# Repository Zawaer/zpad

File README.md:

# ZPad

A 8-key macropad powered by a RP2040, featuring a rotary encoder and a 0.91" OLED display.

Built through [Hack Club](https://hackclub.com)'s Hackpad program. The OLED animation engine in the firmware (bouncing balls, starfield, digital rain, sine waves) and the case are my own.

## Schematic

## PCB

## Bill Of Materials:
- 1x Seeed Studio XIAO RP2040
- 1x EC11 rotary encoder
- 1x 0.91" 128x32 OLED display
- 8x MX-style switches
- 8x White blank DSA keycaps
- 8x Through-hole 1N4148 diodes 
- 4x M3x16mm screws
- 4x M3x5mx4mm heatset inserts

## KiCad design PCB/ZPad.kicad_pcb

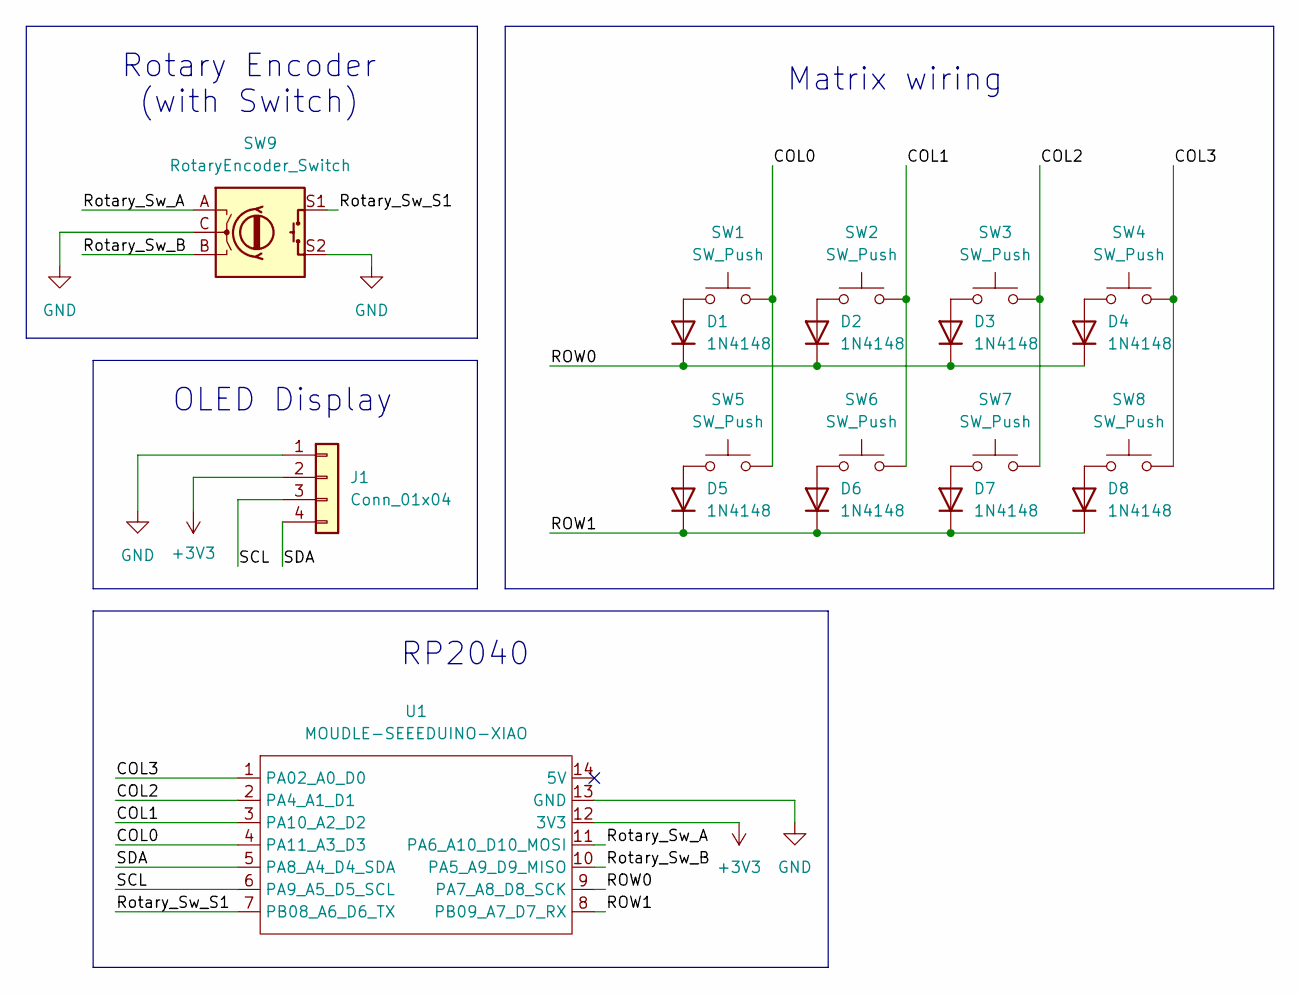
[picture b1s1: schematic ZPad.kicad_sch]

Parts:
D1, D2, D3, D4, D5, D6, D7, D8: 1N4148; D_DO-35_SOD27_P7.62mm_Horizontal
J1: Conn_01x04; SSD1306-0.91-OLED-4pin-128x32
SW1, SW2, SW3, SW4, SW5, SW6, SW7, SW8: SW_Push; SW_Cherry_MX_1.00u_PCB
SW9: RotaryEncoder_Switch; RotaryEncoder_Alps_EC11E-Switch_Vertical_H20mm
U1: MOUDLE-SEEEDUINO-XIAO; XIAO-Generic-Hybrid-14P-2.54-21X17.8MM

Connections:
+3V3: J1.2, U1.12 (3V3)
/COL0: SW1.2, SW5.2, U1.4 (PA11_A3_D3)
/COL1: SW2.2, SW6.2, U1.3 (PA10_A2_D2)
/COL2: SW3.2, SW7.2, U1.2 (PA4_A1_D1)
/COL3: SW4.2, SW8.2, U1.1 (PA02_A0_D0)
/ROW0: D1.1 (K), D2.1 (K), D3.1 (K), D4.1 (K), U1.9 (PA7_A8_D8_SCK)
/ROW1: D5.1 (K), D6.1 (K), D7.1 (K), D8.1 (K), U1.8 (PB09_A7_D7_RX)
/Rotary_Sw_A: SW9.A, U1.11 (PA6_A10_D10_MOSI)
/Rotary_Sw_B: SW9.B, U1.10 (PA5_A9_D9_MISO)
/Rotary_Sw_S1: SW9.S1, U1.7 (PB08_A6_D6_TX)
/SCL: J1.3, U1.6 (PA9_A5_D5_SCL)
/SDA: J1.4, U1.5 (PA8_A4_D4_SDA)
GND: J1.1, SW9.C, SW9.S2, U1.13 (GND)
unnamed: D1.2 (A), SW1.1
unnamed: D2.2 (A), SW2.1
unnamed: D3.2 (A), SW3.1
unnamed: D4.2 (A), SW4.1
unnamed: D5.2 (A), SW5.1
unnamed: D6.2 (A), SW6.1
unnamed: D7.2 (A), SW7.1
unnamed: D8.2 (A), SW8.1

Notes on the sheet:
Matrix wiring
RP2040
OLED Display
Rotary Encoder (with Switch)

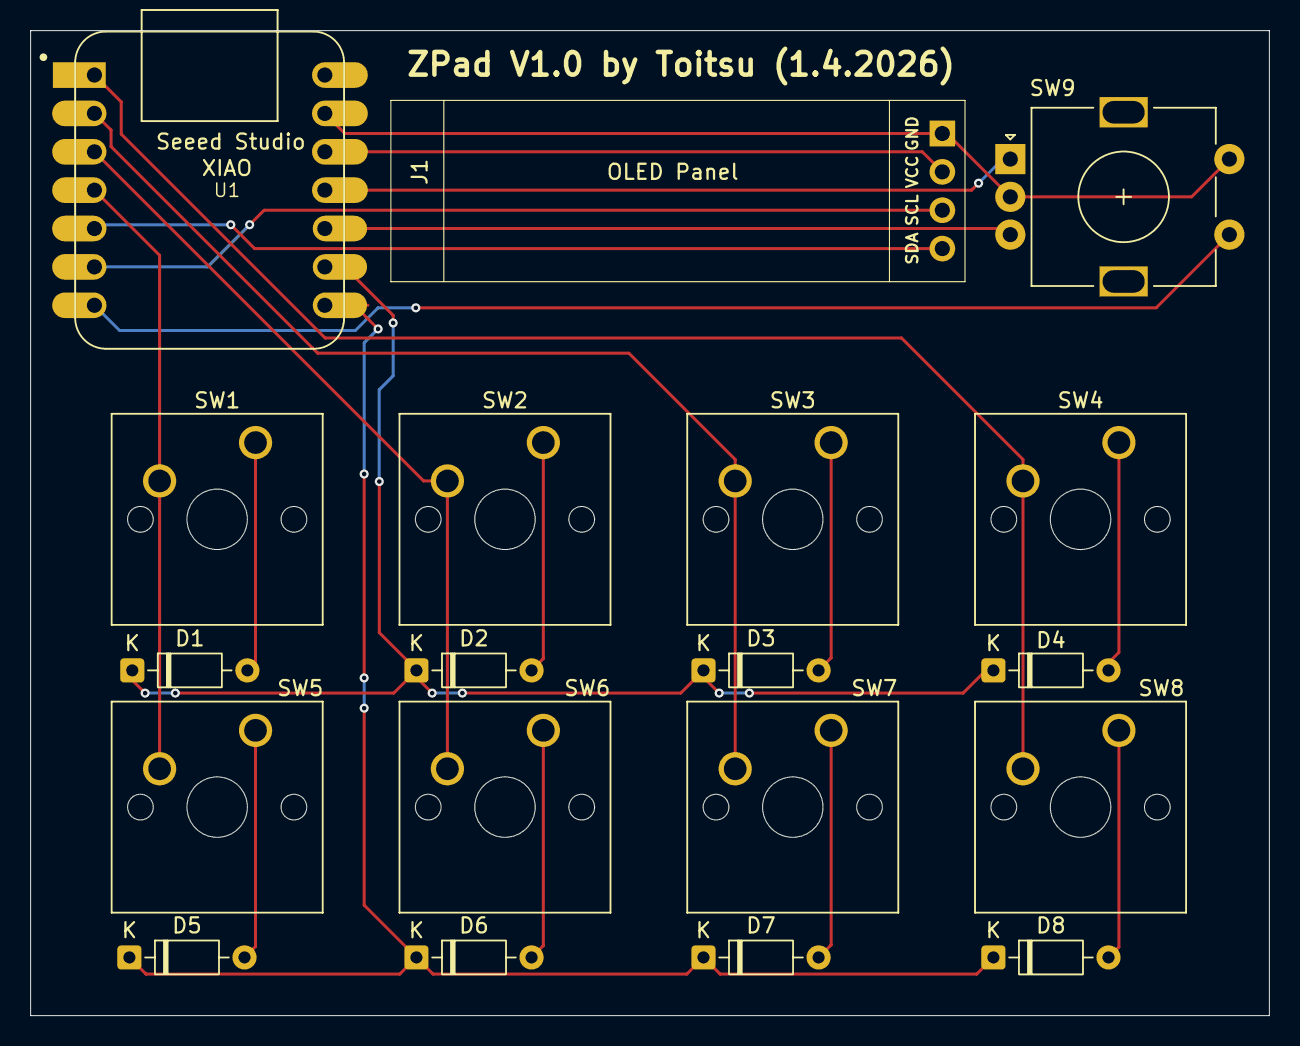
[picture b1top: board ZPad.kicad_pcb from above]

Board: 2 copper layers, 82.0 x 65.2 mm, 19 parts (0 on the bottom side), 21 nets.

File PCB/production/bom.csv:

Designator,Footprint,Quantity,Value,LCSC Part #
"D1, D2, D3, D4, D5, D6, D7, D8",D_DO-35_SOD27_P7.62mm_Horizontal,8,1N4148,
J1,SSD1306-0.91-OLED-4pin-128x32,1,Conn_01x04,
"SW1, SW2, SW3, SW4, SW5, SW6, SW7, SW8",SW_Cherry_MX_1.00u_PCB,8,SW_Push,
SW9,RotaryEncoder_Alps_EC11E-Switch_Vertical_H20mm,1,RotaryEncoder_Switch,
U1,XIAO-Generic-Hybrid-14P-2.54-21X17.8MM,1,MOUDLE-SEEEDUINO-XIAO,

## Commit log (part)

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2026-03-23 Schematic done
2026-03-23 Finally the schematic is actually done
2026-03-29 Routed PCB i think
2026-03-30 Routed PCB again cuz XIAO was flipped
2026-03-30 Finished almost letsgoo
2026-03-30 Added readme
2026-03-30 Added gitignore
2026-03-30 Enhance README with schematic and PCB details
    Added schematic and PCB sections with images to README.
2026-03-30 Finalized everything + added production files
2026-04-01 Fixed stuff according to reviewer
2026-04-01 Update README with new schematic and PCB images
    Added new schematic and PCB images to the README.
2026-06-12 Add new display text features and deprecate old classes
    - Introduced bitmap_label for enhanced label functionality, supporting outlines and scrolling.
    - Added text_box for dynamic text handling with alignment options.
    - Deprecated outlined_label and scrolling_label in favor of bitmap_label.
    - Updated adafruit_displayio_ssd1306 for improved display handling.
    - Ensured compatibility with existing displayio structures and added necessary warnings for deprecated classes.
2026-06-12 Implement cool bouncing ball game
2026-06-12 Refactor animation extension to support multiple scenes and enhance display features
2026-06-12 Final code!!
